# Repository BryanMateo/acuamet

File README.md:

# acuamet
 Repositorio para proyecto de Tesis

Proyecto de Tesis Acuamet

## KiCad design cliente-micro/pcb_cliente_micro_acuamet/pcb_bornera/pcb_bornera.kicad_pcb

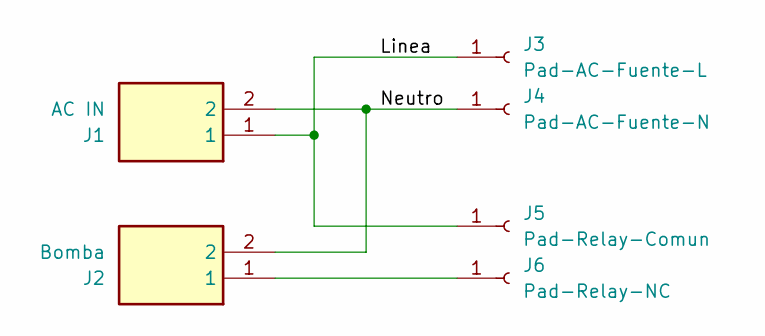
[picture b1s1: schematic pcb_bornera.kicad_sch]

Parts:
J1: AC IN; TB00475002GR; Mouser Part Number 179-TB004-750-02GR
J2: Bomba; TB00475002GR; Mouser Part Number 179-TB004-750-02GR
J3: Pad-AC-Fuente-L; TestPoint_THTPad_D4.0mm_Drill2.0mm
J4: Pad-AC-Fuente-N; TestPoint_THTPad_D4.0mm_Drill2.0mm
J5: Pad-Relay-Comun; TestPoint_THTPad_D4.0mm_Drill2.0mm
J6: Pad-Relay-NC; TestPoint_THTPad_D4.0mm_Drill2.0mm

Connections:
/Linea: J1.1, J3.1, J5.1
/Neutro: J1.2, J2.2, J4.1
unnamed: J2.1, J6.1

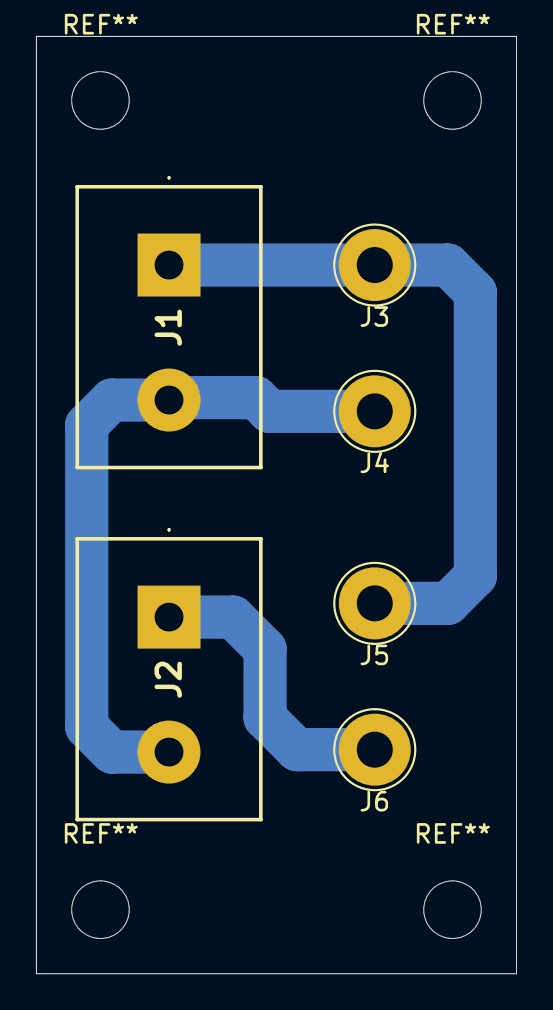
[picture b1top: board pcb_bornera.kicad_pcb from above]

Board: 2 copper layers, 26.7 x 52.1 mm, 6 parts (0 on the bottom side), 3 nets.

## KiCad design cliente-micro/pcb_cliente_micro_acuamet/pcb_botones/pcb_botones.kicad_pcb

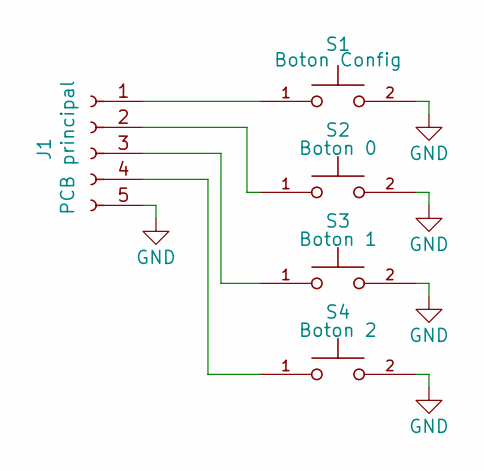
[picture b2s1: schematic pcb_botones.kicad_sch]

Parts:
J1: PCB principal; Molex_KK-254_AE-6410-05A_1x05_P2.54mm_Vertical
S1: Boton Config; BUTT-2_SW_BUTT-2; PARTREV N/A
S2: Boton 0; BUTT-2_SW_BUTT-2; PARTREV N/A
S3: Boton 1; BUTT-2_SW_BUTT-2; PARTREV N/A
S4: Boton 2; BUTT-2_SW_BUTT-2; PARTREV N/A

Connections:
GND: J1.5, S1.2, S2.2, S3.2, S4.2
unnamed: J1.1, S1.1
unnamed: J1.2, S2.1
unnamed: J1.3, S3.1
unnamed: J1.4, S4.1

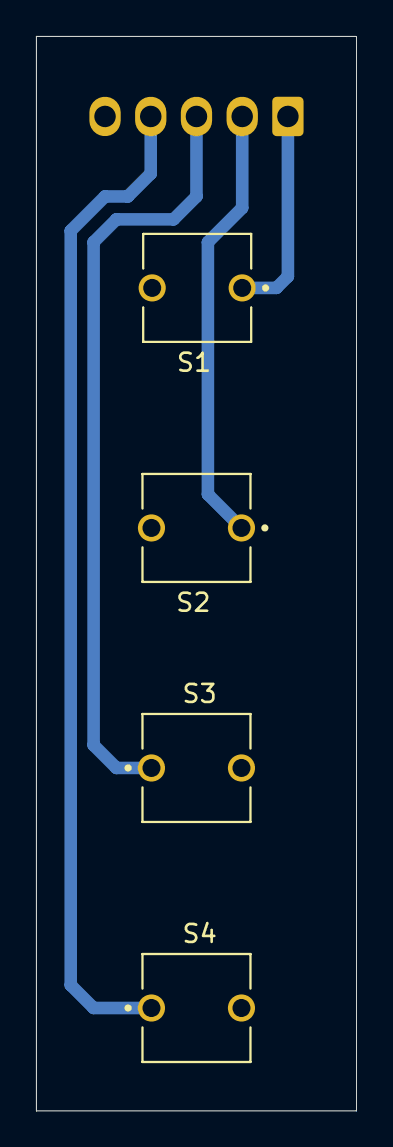
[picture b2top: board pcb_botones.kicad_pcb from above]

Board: 2 copper layers, 17.8 x 59.7 mm, 5 parts (1 on the bottom side), 5 nets.

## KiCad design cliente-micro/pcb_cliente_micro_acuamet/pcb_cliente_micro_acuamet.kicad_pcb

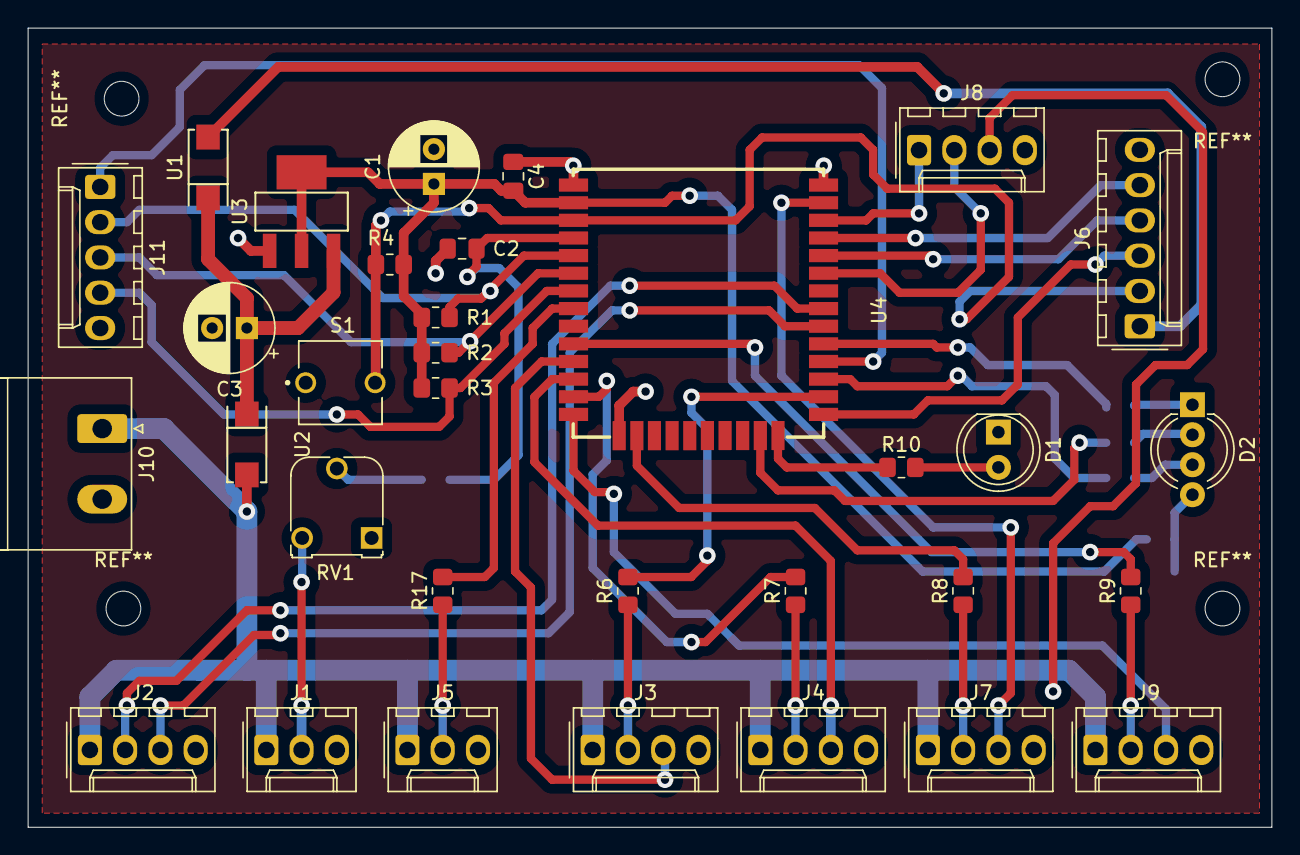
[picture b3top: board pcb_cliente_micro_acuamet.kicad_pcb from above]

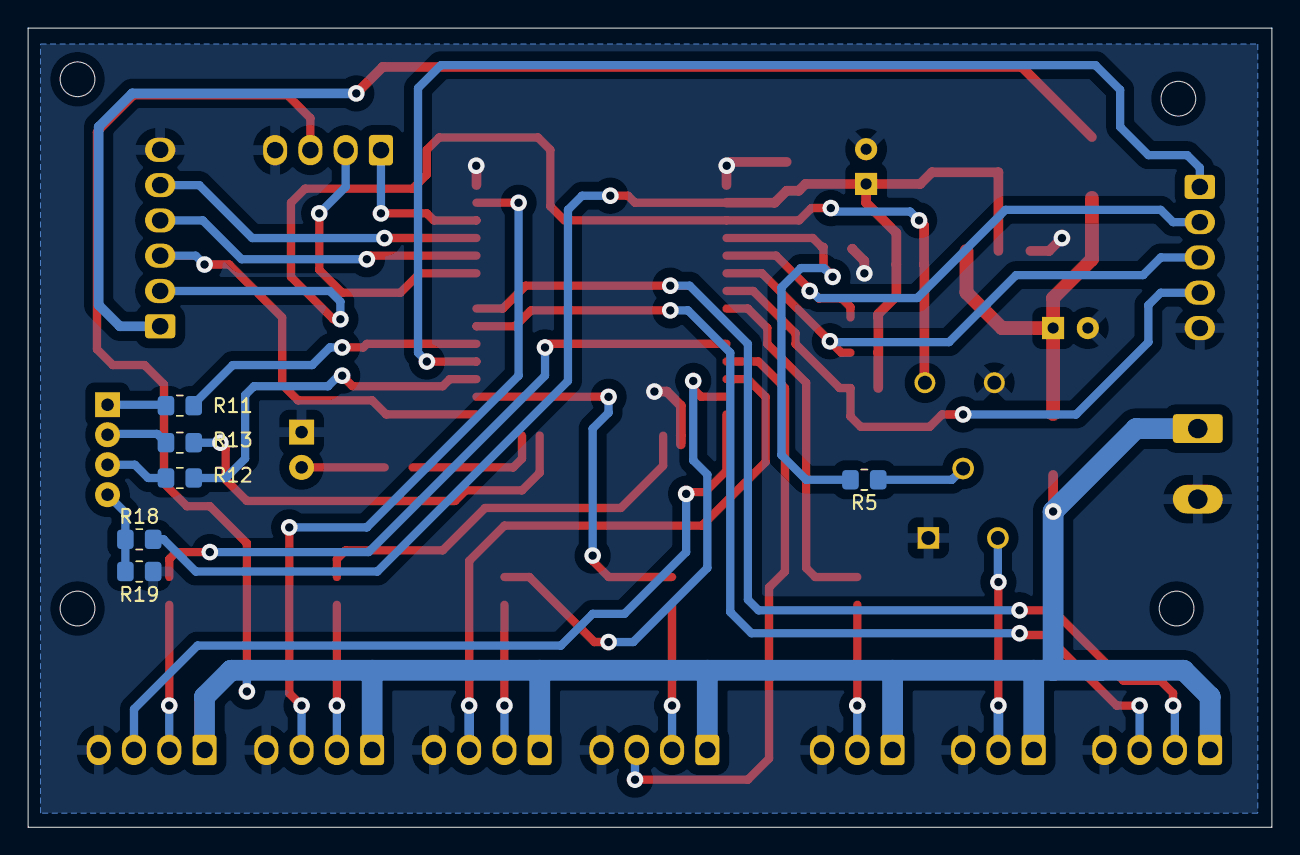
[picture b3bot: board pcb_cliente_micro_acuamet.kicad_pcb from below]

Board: 2 copper layers, 89.5 x 57.5 mm, 39 parts (6 on the bottom side), 43 nets.

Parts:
C1: 22uF 16v; CP_Radial_D6.3mm_P2.50mm
C2, C4: 0.1uF; C_0805_2012Metric_Pad1.18x1.45mm_HandSolder
C3: 10uF 16v; CP_Radial_D6.3mm_P2.50mm
D1: Green LED; LED_D5.0mm_Clear
D2: LED_BRGK; LED_D5.0mm-4_RGB_Wide_Pins
J1: Presion; Molex_KK-254_AE-6410-03A_1x03_P2.54mm_Vertical
J2: Ultrasonico; Molex_KK-254_AE-6410-04A_1x04_P2.54mm_Vertical
J3: Valvula 1; Molex_KK-254_AE-6410-04A_1x04_P2.54mm_Vertical
J4: Valvula 2; Molex_KK-254_AE-6410-04A_1x04_P2.54mm_Vertical
J5: Relay; Molex_KK-254_AE-6410-03A_1x03_P2.54mm_Vertical
J6: Debug; Molex_KK-254_AE-6410-06A_1x06_P2.54mm_Vertical
J7: Valvula 3; Molex_KK-254_AE-6410-04A_1x04_P2.54mm_Vertical
J8: LCD; Molex_KK-254_AE-6410-04A_1x04_P2.54mm_Vertical
J9: Valvula 4; Molex_KK-254_AE-6410-04A_1x04_P2.54mm_Vertical
J10: 5V IN; PhoenixContact_MSTBA_2,5_2-G-5,08_1x02_P5.08mm_Horizontal
J11: Botones; Molex_KK-254_AE-6410-05A_1x05_P2.54mm_Vertical
R1, R2, R3, R4: 10K; R_0805_2012Metric_Pad1.20x1.40mm_HandSolder
R5, R17: 48.7; R_0805_2012Metric_Pad1.20x1.40mm_HandSolder
R6, R7, R8, R9, R10, R11, R12, R13: 1K; R_0805_2012Metric_Pad1.20x1.40mm_HandSolder
R18, R19: 0; R_0805_2012Metric_Pad1.20x1.40mm_HandSolder
RV1: 10K; Potentiometer_Runtron_RM-065_Vertical
S1: BUTT-2; BUTT-2_SW_BUTT-2
U1, U2: M7; SMA_L4.5-W2.7-LS5.1-RD
U3: AMS1117-3.3_C347222; SOT-223-4_L6.5-W3.5-P2.30-LS7.0-BR
U4: ESP32-WROOM-32D; WIFIM-SMD_39P-L25.5-W18.0-P1.27-BL

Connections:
+3.3V: C1.1, C4.2, R1.1, R2.1, R3.1, R4.1, R18.2, U3.2 (VOUT(TAB)), U3.4 (TAB), U4.2 (VDD33)
+5V: J1.1, J2.1, J3.1, J4.1, J5.1, J7.1, J8.3, J9.1, J10.1, U2.2
+5VD: J6.1, U1.2
/EN: J6.2, R4.2, S1.2, U4.3 (EN)
/IO0: J6.3, U4.25 (IO0)
/RXD0: J6.4, U4.34 (RXD0)
/TXD0: J6.5, U4.35 (TXD0)
/boton_0: J11.2, R1.2, U4.5 (SENSOR_VN)
/boton_1: J11.3, R2.2, U4.6 (IO34)
/boton_2: J11.4, R3.2, U4.7 (IO35)
/config_pin: J11.1, U4.28 (IO17)
/flujometro_1: R6.2, U4.26 (IO4)
/flujometro_2: R7.2, U4.13 (IO14)
/flujometro_3: R8.2, U4.16 (IO13)
/flujometro_4: R9.2, U4.10 (IO25)
/lcd_scl: J8.1, U4.36 (IO22)
/lcd_sda: J8.2, U4.33 (IO21)
/pwr_led: R10.1, U4.24 (IO2)
/relay_bomba: R17.2, U4.8 (IO32)
/sens_presion: C2.2, R5.2, U4.4 (SENSOR_VP)
/señal_led_b: R11.1, U4.29 (IO5)
/señal_led_g: R12.1, U4.27 (IO16)
/señal_led_r: R13.1, U4.23 (IO15)
/ultrasonico_echo: J2.3, U4.30 (IO18)
/ultrasonico_trig: J2.2, U4.31 (IO19)
/valvula_1: J3.3, U4.11 (IO26)
/valvula_2: J4.3, U4.12 (IO27)
/valvula_3: J7.3, U4.37 (IO23)
/valvula_4: J9.3, U4.14 (IO12)
GND: C1.2, C2.1, C3.2, C4.1, D1.1 (K), J1.3, J2.4, J3.4, J4.4, J5.3, J6.6, J7.4, J8.4, J9.4, J10.2, J11.5, R19.1, RV1.1, S1.1, U3.1 (ADJ(GND)), U4.1 (GND), U4.15 (GND), U4.38 (GND), U4.39 (GND)
unnamed: D1.2 (A), R10.2
unnamed: D2.1 (BA), R11.2
unnamed: D2.3 (GA), R12.2
unnamed: D2.4 (K), R18.1, R19.2
unnamed: D2.2 (RA), R13.2
unnamed: J1.2, RV1.3
unnamed: J3.2, R6.1
unnamed: J4.2, R7.1
unnamed: J5.2, R17.1
unnamed: J7.2, R8.1
unnamed: J9.2, R9.1
unnamed: R5.1, RV1.2
VCC: C3.1, U1.1, U2.1, U3.3 (VIN)

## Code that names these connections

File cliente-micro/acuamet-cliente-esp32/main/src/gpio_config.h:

#ifndef GPIO_CONFIG_H
#define GPIO_CONFIG_H
#include "../main.h"

extern bool gpio_inicializado;
// Entradas
#define config_pin 17 // (GPIO 17) Pin para subir modo configuracion
#define boton_0 39    // (GPIO 39) Pin boton 0 - hacer pullup en pcb
#define boton_1 34    // (GPIO 34) Pin boton 1 - hacer pullup en pcb
#define boton_2 35    // (GPIO 35) Pin boton 2 - hacer pullup en pcb

#define pin_sensor_presion ADC_CHANNEL_0 // (GPIO 36) Pin Sensor VP - capacitor de desacople 0.1uf

#define pin_flujometro_1 4  // (GPIO 4) Pin pulse counter para flujometro
#define pin_flujometro_2 14 // (GPIO 14) Pin pulse counter para flujometro
#define pin_flujometro_3 13 // (GPIO 13) Pin pulse counter para flujometro
#define pin_flujometro_4 25 // (GPIO 25) Pin pulse counter para flujometro

// Salidas
#define pin_pwr_on_led 2    // (GPIO 2) Pin para indicar PWR
#define pin_signal_led_r 15 // (GPIO 15) Pin señal Wifi R
#define pin_signal_led_g 16 // (GPIO 16) Pin señal Wifi G
#define pin_signal_led_b 5  // (GPIO 5) Pin señal Wifi B

#define pin_valvula_1 26 // (GPIO 26) Pin PWM para servovalvula
#define pin_valvula_2 27 // (GPIO 27) Pin PWM para servovalvula
#define pin_valvula_3 23 // (GPIO 23) Pin PWM para servovalvula
#define pin_valvula_4 12 // (GPIO 12) Pin PWM para servovalvula

#define pin_relay_bomba 32 // (GPIO 32) Pin del relay de encendido/apagado bomba

#define pin_lcd_scl 22 // (GPIO 22) Pin I2C para LCD
#define pin_lcd_sda 21 // (GPIO 21) Pin I2C para LCD

// Sensor cisterna Ultrasonico
#define pin_ultrasonico_cisterna_echo 18 // (GPIO 18) Pin echo para sensor ultrasonico nivel cisterna
#define pin_ultrasonico_cisterna_trig 19 // (GPIO 19) Pin trig para sensor ultrasonico nivel cisterna

// Funciones
void gpio_init(); // Funcion para inicializar los GPIO como I/O

#endif

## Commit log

2025-02-10 configuracion inicial plataforma
    Punto de partida para la api y la pagina web del proyecto.
2025-02-12 parametros iniciales
2025-03-17 Punto de partida ESP32
    1. AP-Pag web-Wifi config
    2. Conexion MQTT
    3. Creacion de topicos individuales con la MAC unica del ESP32
2025-03-18 FSM Implementada
    Limpieza del codigo y organizacion de las librerias y los headers.
    Implementacion de la estructura de la FSM en un task, y la definicion de los estados, faltan agregar las codiciones y return adecuados en cada una de las funciones/estados.
2025-03-18 Optimizacion Main.c, MQTT
    Limpieza, organizacion y optimizacion del codigo.
    Inclusion del MQTT al FSM, y creacion de flags de mqtt y wifi connected.
2025-03-19 Interrupciones para medir flujo
    Se utilizo interrupciones a la CPU con cada pulso del flujometro para sumar la cantidad de pulsos y calcular el flujo.
2025-03-20 Reemplazado las interrupciones por un contador por hardware PCNT.
    Se cambio el conteo de pulsos mediante interrupciones, al contador por hardware del esp32 PCNT.
2025-03-20 Implementado el contador de pulsos y litros en un task.
2025-03-20 Optimizacion.
2025-03-22 Implementacion sens ultrasonico.
    Cambiado contador_pulsos a sensores.
    Implementado sensor ultrasonico con medida por promedio.
    Optimizacion de task.
2025-03-25 Sensor de presion agregado
    Se agrego la funcion para leer el sensor de presion usando ADC oneshot.
    Se cambio la tabla de particion del ESP de 1mb a 1.5mb.
2025-03-25 Implementados las estructuras de los sensores y salidas
    Creada la funcion de leer los pulsos de los flujometros y convertir a galones.
2025-03-26 Cambios a la fsm, y sensor de presion.
    Agregados estados online y offline.
    Sensor de presion por promedio.
2025-03-29 Agregado llave identificadora.
    Agregado llave o key unica para identificar cada usuario en los clientes.
    Agregada la configuracion de la llave en el cliente.
    Creacion de registro en la base de datos por la api, de cliente nuevo o actualizacion de llave de uno existente, y inicializacion de topicos de control.
2025-03-30 LCD implementado
    Implementado los comandos de control para el LCD
2025-04-07 Version 1 del PCB
    Version 1 del PCB.
    Limpieza de codigo y comentarios
2025-04-12 Version final PCB
    Version revisada y corregida
2025-04-12 Archivo .STEP PCB
    Archivo step del PCB actualizado
2025-04-13 Carcasa sensor ultrasonico listo
2025-04-13 Directorios
2025-04-13 Todos los diseños hasta la fecha
2025-04-13 Control de salidas
    Implementado control de salidas.
    Agregada estructura de flags para control, wifi, etc.
    Optimizado y funcionando json para la suscripcion mqtt.
2025-04-14 Correcion de recursos 3D
2025-04-14 Servovalvula v2
    Rediseño de servovalvula
2025-04-14 PCB para botones cliente
2025-04-14 STL Piezas servovalvula v2
2025-04-15 PCB borneras AC
    PCB para entrada AC y salida de control por relay de la bomba en rango 110-240V AC.
2025-04-15 Organizacion de directorios.
2025-04-16 Case terminado
    Version 1 del case terminado
2025-04-16 Actualizado Servo Valvula v2
2025-04-17 Conteo de consumo offline y en el servidor.
    Optimizada la FSM: Anulado estado wificonn, se inicializa el STA y el cliente mqtt en el init. Wifi y MQTT se mantienen reconectando en sus task.
    Estado online con un token para evitar sumar datos erroneos, que se guarda en la base de datos.
    Estado offline que guarda consumo en la NVS y el token anterior si existe. Posible token redundante en la flash (se podria eliminar de la nvs y solo guardar consumos).
    Implementacion en la api para sumar el consumo acumulado de cada cliente y asignar los token.
    Optimizacion general de codigo del ESP32.
2025-04-17 Task para LCD
    Task que va a manejar el LCD dependiendo del estado actual de la FSM
2025-04-18 Consumo acumulado online LCD
    Optimizacion de api.
    Consumo acumulado en lcd.
2025-04-21 Fix servovalvula
2025-04-23 Plot PCB
2025-04-28 Terminacion de pagina web v1
2025-04-28 Pagina web ya se comunica con api, enciende y apaga bomba y valvulas
